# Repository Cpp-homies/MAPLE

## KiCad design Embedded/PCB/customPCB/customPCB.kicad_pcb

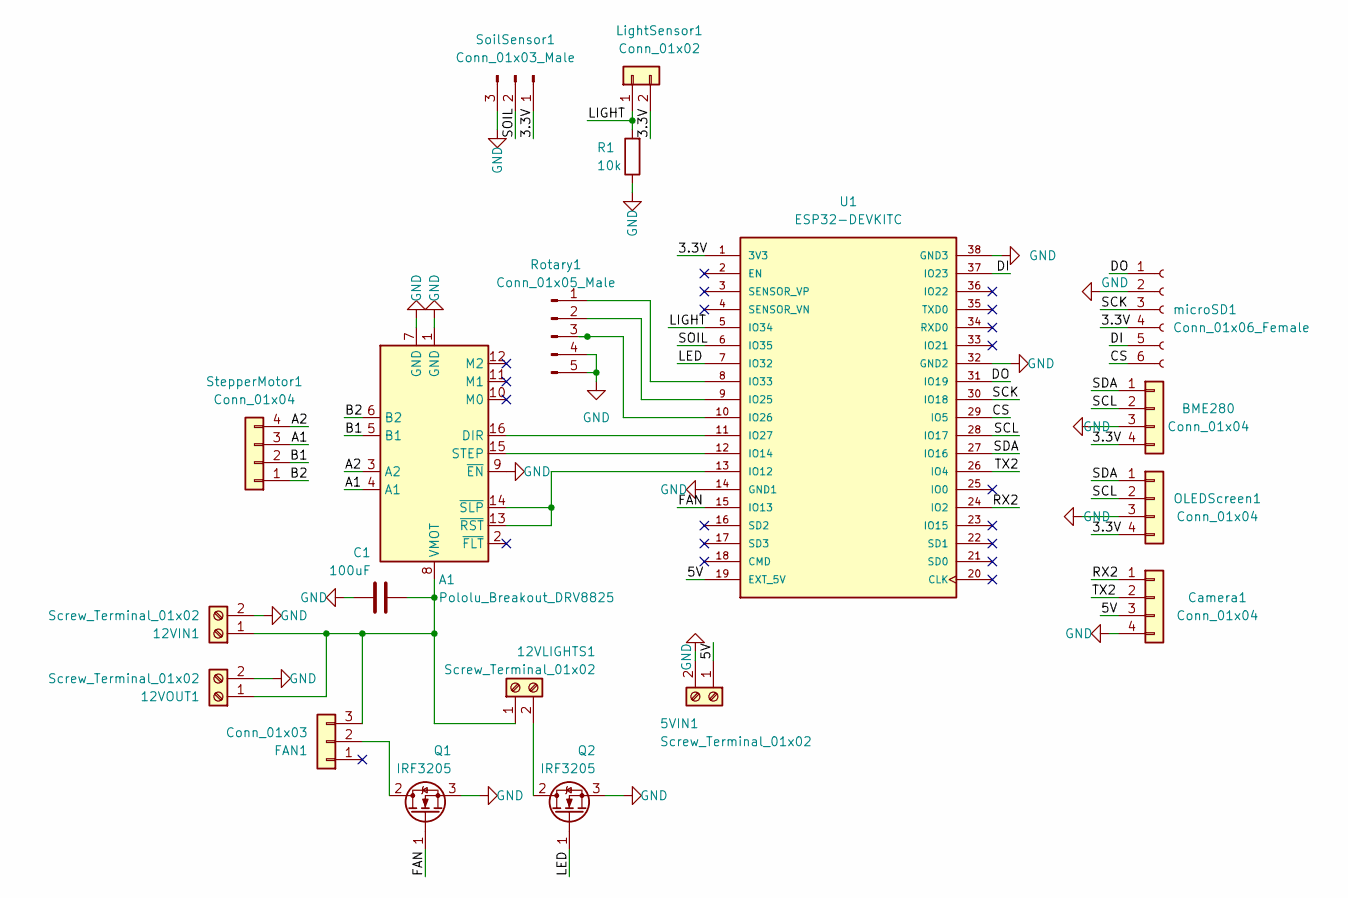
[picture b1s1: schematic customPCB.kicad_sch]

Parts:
5VIN1, 12VIN1, 12VLIGHTS1, 12VOUT1: Screw_Terminal_01x02; 691502710002
A1: Pololu_Breakout_DRV8825; Pololu_Breakout-16_15.2x20.3mm
BME280: Conn_01x04; JST_XH_B4B-XH-A_1x04_P2.50mm_Vertical
C1: 100uF; C_0805_2012Metric
Camera1: Conn_01x04; JST_XH_B4B-XH-A_1x04_P2.50mm_Vertical
FAN1: Conn_01x03; JST_XH_B3B-XH-A_1x03_P2.50mm_Vertical
LightSensor1: Conn_01x02; JST_XH_B2B-XH-A_1x02_P2.50mm_Vertical
OLEDScreen1: Conn_01x04; JST_XH_B4B-XH-A_1x04_P2.50mm_Vertical
Q1, Q2: IRF3205; TO254P1524X483-4N
R1: 10k; R_0805_2012Metric
Rotary1: Conn_01x05_Male; PinHeader_1x05_P2.54mm_Vertical
SoilSensor1: Conn_01x03_Male; PinHeader_1x03_P2.54mm_Vertical
StepperMotor1: Conn_01x04; JST_XH_B4B-XH-A_1x04_P2.50mm_Vertical
U1: ESP32-DEVKITC; MODULE_ESP32-DEVKITC; PARTREV N/A
microSD1: Conn_01x06_Female; PinSocket_1x06_P2.54mm_Vertical

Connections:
/3.3V: BME280.4, LightSensor1.2, OLEDScreen1.4, SoilSensor1.1, U1.1 (3V3), microSD1.4
/5V: 5VIN1.1, Camera1.3, U1.19 (EXT_5V)
/A1: A1.4 (A1), StepperMotor1.3
/A2: A1.3 (A2), StepperMotor1.4
/B1: A1.5 (B1), StepperMotor1.2
/B2: A1.6 (B2), StepperMotor1.1
/CS: U1.29 (IO5), microSD1.6
/DI: U1.37 (IO23), microSD1.5
/DO: U1.31 (IO19), microSD1.1
/FAN: Q1.1 (G), U1.15 (IO13)
/LED: Q2.1 (G), U1.7 (IO32)
/LIGHT: LightSensor1.1, R1.2, U1.5 (IO34)
/RX2: Camera1.1, U1.24 (IO2)
/SCK: U1.30 (IO18), microSD1.3
/SCL: BME280.2, OLEDScreen1.2, U1.28 (IO17)
/SDA: BME280.1, OLEDScreen1.1, U1.27 (IO16)
/SOIL: SoilSensor1.2, U1.6 (IO35)
/TX2: Camera1.2, U1.26 (IO4)
GND: 5VIN1.2, 12VIN1.2, 12VOUT1.2, A1.1 (GND), A1.7 (GND), A1.9 (~EN), BME280.3, C1.1, Camera1.4, OLEDScreen1.3, Q1.3 (S), Q2.3 (S), R1.1, Rotary1.4, Rotary1.5, SoilSensor1.3, U1.14 (GND1), U1.32 (GND2), U1.38 (GND3), microSD1.2
unnamed: 12VIN1.1, 12VLIGHTS1.1, 12VOUT1.1, A1.8 (VMOT), C1.2, FAN1.3
unnamed: 12VLIGHTS1.2, Q2.2 (D)
unnamed: A1.13 (~RST), A1.14 (~SLP), U1.13 (IO12)
unnamed: A1.15 (STEP), U1.12 (IO14)
unnamed: A1.16 (DIR), U1.11 (IO27)
unnamed: FAN1.2, Q1.2 (D)
unnamed: Rotary1.1, U1.8 (IO33)
unnamed: Rotary1.2, U1.9 (IO25)
unnamed: Rotary1.3, U1.10 (IO26)

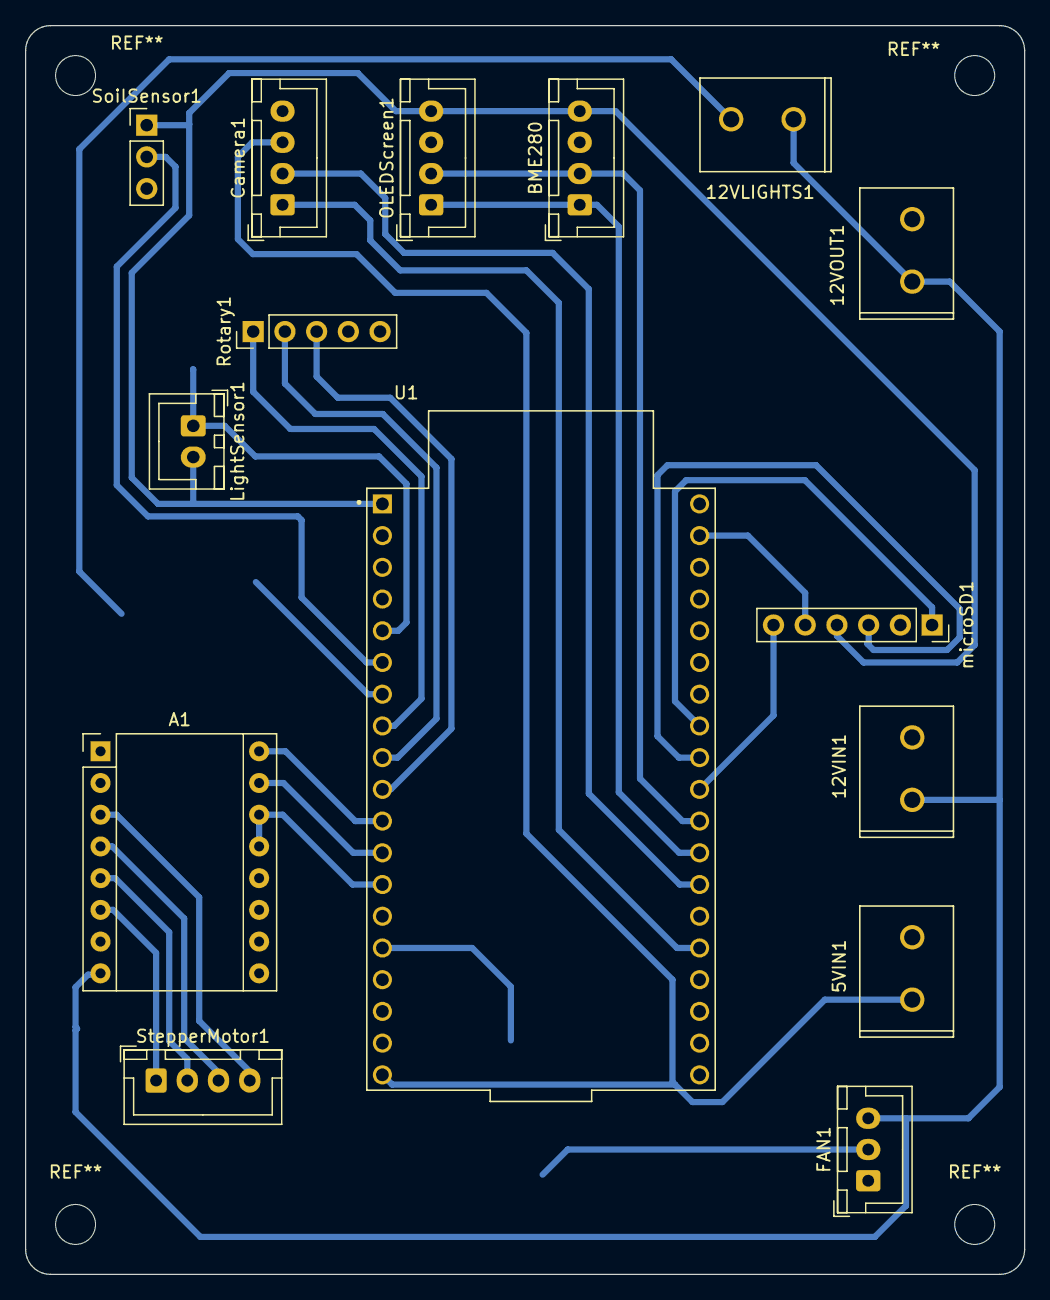
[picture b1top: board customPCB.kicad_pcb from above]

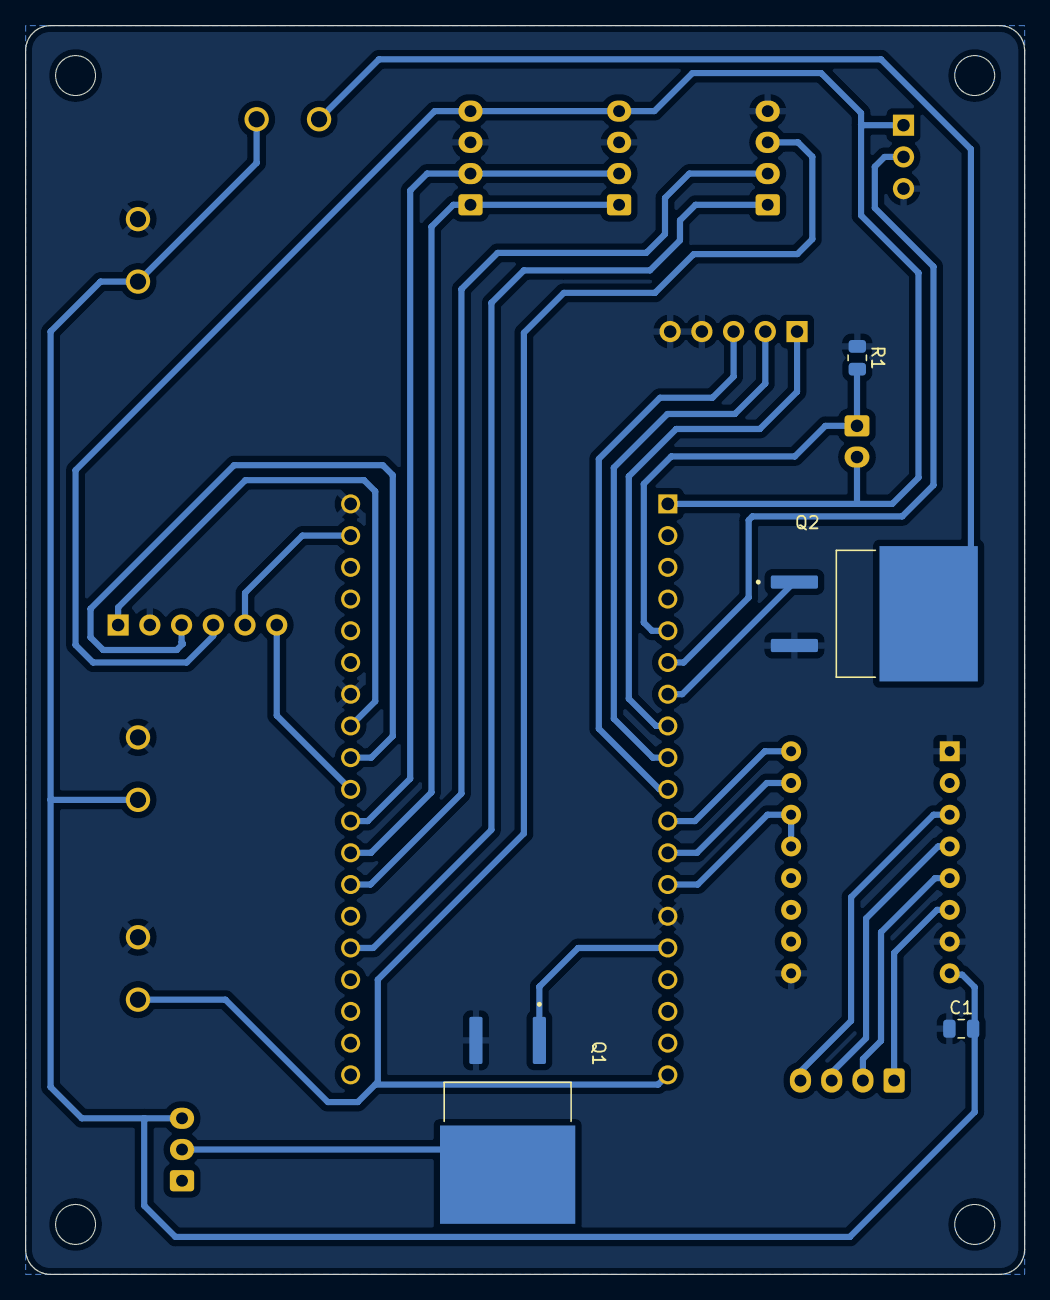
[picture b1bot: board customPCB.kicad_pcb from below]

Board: 2 copper layers, 80.0 x 100.0 mm, 19 parts (4 on the bottom side), 28 nets.

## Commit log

2023-03-01 Readme update, added old documents
2023-03-01 restructured documents folder, added an interview document
2023-03-03 Added basic server and esp client code
2023-03-06 Added PATCH request
2023-03-08 Wrap connect WiFi and data sending in a function
2023-03-08 Fixed small timestamp bug
2023-03-08 Change the database and request data type to Float
2023-03-08 Added API method for getting the data table in JSON
2023-03-08 Added exception handling for invalid argument values in the requests
2023-03-08 Main script for ESP32-S2 to send sensor data and control the lights
2023-03-22 Switched to ESP32-WROOM-32E (pin changes), added soil sensor and pump control
2023-03-23 Added pump power cut off
2023-03-24 Added wifi config and MAPLE login credentials - not working yet
2023-03-24 WiFi config fix and added a fan
2023-03-24 Code cleanup, fan control fix
2023-03-26 Pin changes, added an microSD card breakout with basic code
2023-03-26 Added camera UART connection to ESP for WiFi login.
2023-03-26 Added camera file
2023-03-27 Added example rotary sketch
2023-03-30 Added HOST and PORT variable for better management
2023-03-30 Added a listener that runs on a different core The listener runs on core 0 (the void loop function runs on core 1) and listen to incoming requests from the cloud.
2023-03-30 Added some code from last commit that I forgot to add
2023-03-31 Added app
2023-03-31 Added live data put request
2023-03-31 Added requirements.txt file
2023-03-31 Fixed variable sharing bug between request threads
2023-03-31 improved graph and overall styling
2023-04-01 Implement asynchronousity for get request To serve both the App and ESP requests simultaneously
    The live data request will wait until live data from the ESP has been updated
2023-04-05 Added soil humidity and change the old humidity key to air_humidity
2023-04-05 Added changelogs.md to keep track of the changes made to the API
2023-04-05 Adjust the ESP code according to the new changes in 9f07ddb
2023-04-05 Added user ID support for GET, PUT, and get_datatable methods
2023-04-05 Added Client class and change related functions accordingly
2023-04-05 Fixed minor bug on data requests with User ID
2023-04-05 Added basic rotary encoder functionality
2023-04-05 Merged the Cloud ESP code into the embedded side
2023-04-05 Added SHA-256 string hashing for the ESP
2023-04-05 Updated main and cam uart connection
2023-04-07 Implement user register PUT request
2023-04-07 Implement login GET request
2023-04-07 Implement PATCH request for changing password
2023-04-07 Added checks to prevent unauthorized requests
2023-04-07 Minor correction to the change log
2023-04-09 Fixed camera UART connection, added SDcard data logging
2023-04-09 Code cleanup and comments
2023-04-09 Converted analog readings to humidity %, added boot screen text
2023-04-11 gitignore
2023-04-11 added login popup
2023-04-11 Implement device side authentication
2023-04-11 Change the device side authentication implementation
2023-04-11 added custom border styling and register popup
2023-04-12 Replaced dummy data with live data readings
2023-04-12 Minor fix
2023-04-12 Fixed minor bug in PUT request
2023-04-12 Added basic backup code
2023-04-12 Wrap the backup code in a function and make it reuseable for all filetypes
2023-04-12 Implement periodical data backup
2023-04-12 added login and register authentication with backend, minor style improvements, improved usability
2023-04-12 Fixed session data retention bug for user authentication
2023-04-12 Added server flask_session file to gitignore
2023-04-13 added hashing to user IDs and passwords, minor style improvements, fixed graph saying loading data when data is not being loaded, added footer
2023-04-13 Added all 3D models and laser cutting files
2023-04-14 Added expiry time for the Flask session
2023-04-14 Disable HTTPClient reuse for the ESP - The reuse causes heapoverflow after a while
2023-04-14 Moved the Backup client to its own folder
2023-04-14 Added GET method for checking the server online status
2023-04-14 minor improvements
2023-05-04 Testing pin changes
2023-05-04 Pin number fix
2023-05-05 Fixed the memory error with the HTTPClient object
2023-05-05 Implemented delete-all method - For deleting all sensor data associated with a user
2023-05-10 Change database timestamp type from String to DateTime
2023-05-15 Minor fixes for PCB testing
2023-05-15 Apply a tested fix for the HTTP Client that previously causes crashing Original commit from cloud branch f12ecc5
2023-05-16 Soil sensor calibration improvement and creating plant check interval
2023-05-16 Added stepper library for later use
2023-05-17 Calibrated sensors, added some automation options, added reboot option
2023-05-17 Added PCB KiCad model
2023-05-19 Added a rotary menu, offline mode and reboot option.
2023-05-21 made app installable in chrome
2023-05-21 made it installable on most browsers
2023-05-22 Offline mode and menu bug fixes
2023-05-22 First draft of offline menu and control
2023-05-22 Simplified light control
2023-05-22 Improved watering control
2023-05-23 Set local timezone, redesigned offline menu, added fan control option, disabled menu for online mode.
2023-05-24 Complete method for requesting data in a certain time range
2023-05-24 Implement a shorthand 'now' to query data from a certain time to the current time
2023-05-25 Allow CORS
2023-05-25 style update, bug fixes
2023-05-26 Added partial ESP code for picture sending
2023-05-26 Added base image receiving code on the server side
2023-05-26 Fix date formating bug in getdatatable - Due to the change from string to DATETIME type, using the timestamp attribute directly as return value is no longer sufficient. This commit reformat the datet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
2023-05-26 Fix data sending bug - Increase the JSON payload size to fit the username and password
2023-05-26 Adjusted pump timings, uncommented timezone setting, updated camera interval
2023-05-26 Complete image receiving code for the server side
2023-05-27 Complete ESP picture sending code
2023-05-27 Use the filename in the SD card as the filename for the server - Previous name was the default 'esp32-cam'
2023-05-27 Added method for accessing the photos on the server
2023-05-27 Added code for picture sending to cam.ino
2023-05-27 Minor changes to photo sending - Added support for username - User the filename instead of filepath for naming the file on the server - Send photo after saving it to the SD card
2023-05-27 Added server side user directory support
2023-05-27 Added GET method for querying a list of filenames for user images
2023-05-27 Changed pumping variables
2023-05-27 Sort the return filenames in get_imageList before returning the list
2023-05-27 Added method for querying the most recent image
2023-05-27 Adjust image uploads before saving - Change extension to .webp - Shrink dimension to 800x600
2023-05-27 Add the Cloud image folder to .gitignore
2023-05-27 Averageing of sensor readings
2023-05-27 controllers added, new style, photofeed added, chart fixed, chart soil humidity added
2023-05-28 Implemented remote control methods
2023-05-28 Quick update
2023-05-28 Implemented device side remote control handling
2023-05-28 Implemented periodical update for the control parameters on the server
2023-05-28 Make lights turn on before camera
2023-05-28 Implemented control parameter update method - For the ESP to update the parameters stored on the server to the up-to-date ones
2023-05-28 Implemented get methods for control parameters
2023-05-29 Fix the SET methods for remote control
2023-05-29 Fix return status for SET control methods
2023-05-30 New files
2023-05-30 Last changes before the presentation
2023-05-30 bug fixes, improvements
2023-05-30 too complex...
2023-06-06 Create LICENSE
